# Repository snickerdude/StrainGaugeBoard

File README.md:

# StrainGaugeBoard
Multi channel strain gauge data acquisition board

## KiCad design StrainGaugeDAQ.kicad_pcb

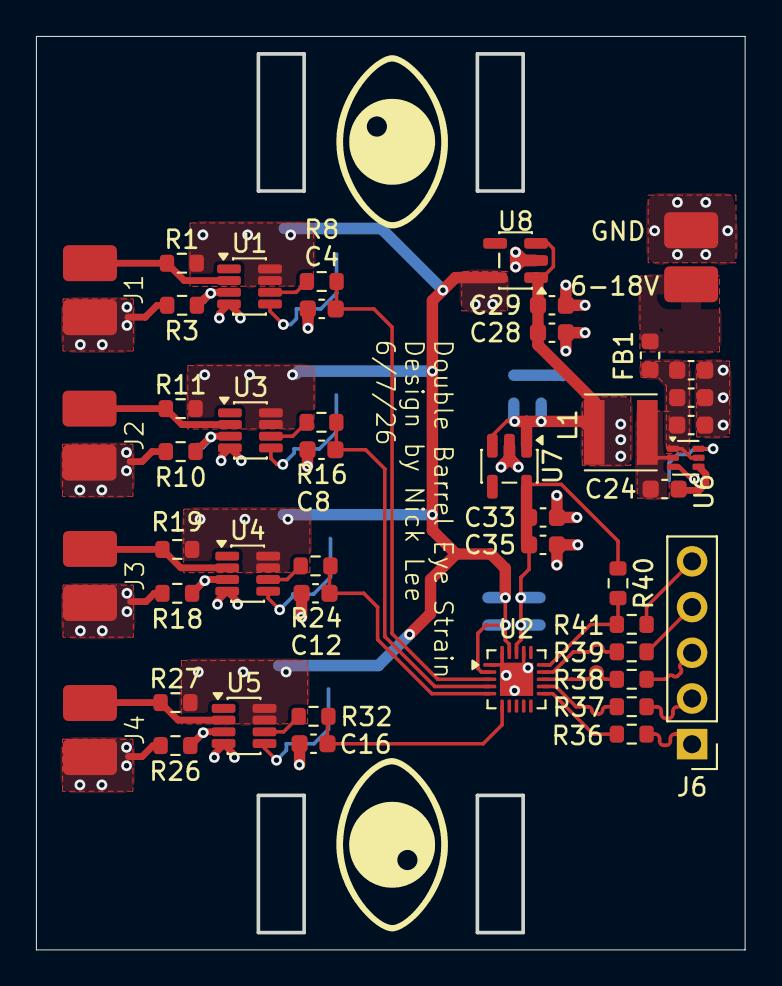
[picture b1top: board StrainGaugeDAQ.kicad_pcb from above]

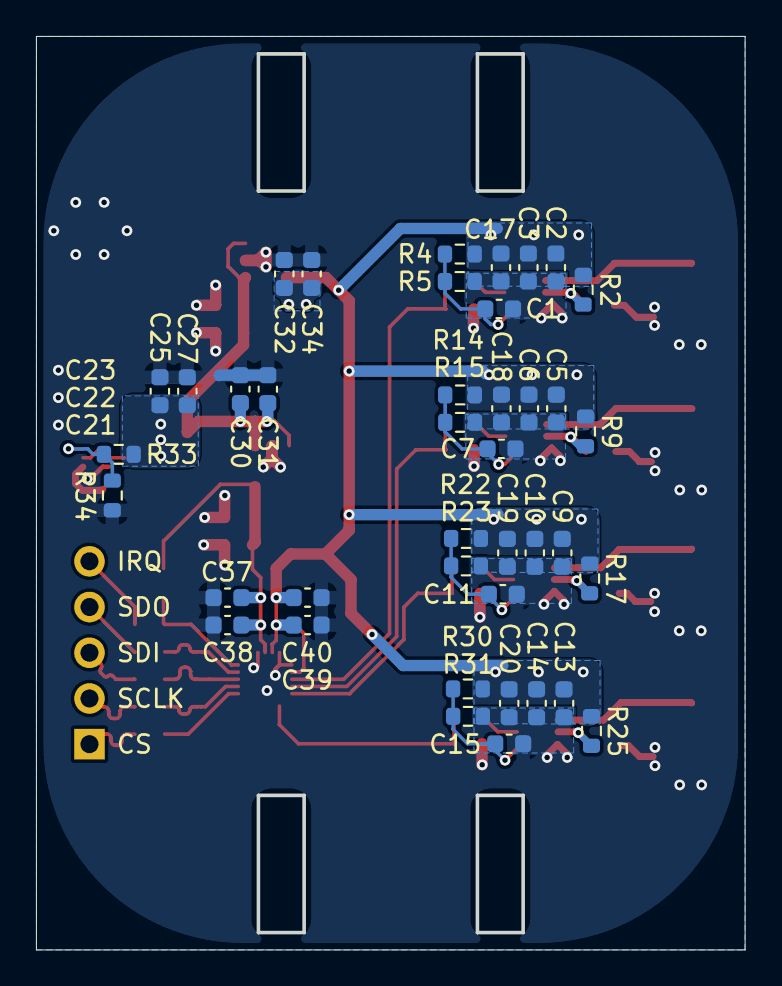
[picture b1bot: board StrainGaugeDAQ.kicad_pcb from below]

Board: 2 copper layers, 39.2 x 50.6 mm, 88 parts (40 on the bottom side), 39 nets.

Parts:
C1, C2, C3, C5, C6, C7, C9, C10, C11, C13, C14, C15, C17, C18, C19, C20, C23, C24, C27, C28, C31, C32, C33, C34, C35, C37, C39: 100n; C_0603_1608Metric
C4, C8, C12, C16: C; C_0603_1608Metric
C21, C22, C25: 22u; C_0603_1608Metric
C29, C30, C38, C40: 10u; C_0603_1608Metric
FB1: FerriteBead; L_0603_1608Metric
H1, H2: MountingScrew; EyePicture
J1: IN1; SolderPad_01x02
J2: IN2; SolderPad_01x02
J3: IN3; SolderPad_01x02
J4: IN4; SolderPad_01x02
J5: 6-18V; SolderPad_01x02
J6: SPI+INT; PinHeader_1x05_P2.54mm_Vertical
L1: 3.3u; L_Vishay_IFSC-1515AH_4x4x1.8mm
R1, R2, R3, R8, R9, R10, R11, R16, R17, R18, R19, R24, R25, R26, R27, R32: R_US; R_0603_1608Metric
R4, R5, R14, R15, R22, R23, R30, R31, R34, R40: 10k; R_0603_1608Metric
R33: 52.3k; R_0603_1608Metric
R36, R37, R38, R39, R41: 10; R_0603_1608Metric
U1, U3, U4, U5: INA351CDSIDSGR; TSOT-23-8
U2: MCP3562RT-E/NC; UQFN-20-1EP_3x3mm_P0.4mm_EP1.85x1.85mm
U6: AP62150Z6; SOT-563
U7, U8: AP2127K-3.3; SOT-23-5

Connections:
5V: C25.1, C27.1, C28.1, C29.1, C30.1, C31.1, L1.2, R33.1, U7.1 (VIN), U7.3 (EN), U8.1 (VIN), U8.3 (EN)
/Amp1/In+: J1.2, R1.2, U1.2 (IN-)
/Amp1/Vout: C4.1, R8.1, U2.3 (CH0)
/Amp2/In+: J2.2, R11.2, U3.2 (IN-)
/Amp2/Vout: C8.1, R16.1, U2.4 (CH1)
/Amp3/In+: J3.2, R19.2, U4.2 (IN-)
/Amp3/Vout: C12.1, R24.1, U2.5 (CH2)
/Amp4/In+: J4.2, R27.2, U5.2 (IN-)
/Amp4/Vout: C16.1, R32.1, U2.6 (CH3)
/PD/VCC: FB1.1, J5.2
AVDD: C2.1, C3.1, C5.1, C6.1, C9.1, C10.1, C13.1, C14.1, C17.2, C18.2, C19.2, C20.2, C32.1, C34.1, C39.2, C40.2, R1.1, R2.1, R4.1, R9.1, R11.1, R14.1, R17.1, R19.1, R22.1, R25.1, R27.1, R30.1, U1.7 (V+), U1.8 (*SHDN), U2.2 (REFIN+/OUT), U2.19 (AVDD), U3.7 (V+), U3.8 (*SHDN), U4.7 (V+), U4.8 (*SHDN), U5.7 (V+), U5.8 (*SHDN), U8.5 (VOUT)
DVDD: C33.1, C35.1, C37.2, C38.2, R40.1, U2.18 (DVDD), U7.5 (VOUT)
GND: C1.2, C2.2, C3.2, C4.2, C5.2, C6.2, C7.2, C8.2, C9.2, C10.2, C11.2, C12.2, C13.2, C14.2, C15.2, C16.2, C17.1, C18.1, C19.1, C20.1, C21.2, C22.2, C23.2, C25.2, C27.2, C28.2, C29.2, C30.2, C31.2, C32.2, C33.2, C34.2, C35.2, C37.1, C38.1, C39.1, C40.1, J1.1, J2.1, J3.1, J4.1, J5.1, R3.2, R5.2, R10.2, R15.2, R18.2, R23.2, R26.2, R31.2, R34.2, U1.4 (V-), U2.1 (REFIN-), U2.17 (DGND), U2.20 (AGND), U2.21 (GND), U3.4 (V-), U4.4 (V-), U5.4 (V-), U6.3 (GND), U7.2 (GND), U8.2 (GND)
unnamed: J6.1, R36.2
unnamed: J6.2, R37.2
unnamed: J6.3, R38.2
unnamed: J6.4, R39.1
unnamed: J6.5, R41.1
unnamed: R2.2, R3.1, U1.3 (IN+)
unnamed: R8.2, U1.6 (OUT)
unnamed: C1.1, R4.2, R5.1, U1.5 (REF)
unnamed: R36.1, U2.11 (*CS)
unnamed: R40.2, R41.2, U2.15 (*IRQ/MDAT)
unnamed: R37.1, U2.12 (SCK)
unnamed: R38.1, U2.13 (SDI)
unnamed: R39.2, U2.14 (SDO)
unnamed: R9.2, R10.1, U3.3 (IN+)
unnamed: R16.2, U3.6 (OUT)
unnamed: C7.1, R14.2, R15.1, U3.5 (REF)
unnamed: R17.2, R18.1, U4.3 (IN+)
unnamed: R24.2, U4.6 (OUT)
unnamed: C11.1, R22.2, R23.1, U4.5 (REF)
unnamed: R25.2, R26.1, U5.3 (IN+)
unnamed: R32.2, U5.6 (OUT)
unnamed: C15.1, R30.2, R31.1, U5.5 (REF)
unnamed: C24.2, U6.4 (BST)
unnamed: C21.1, C22.1, C23.1, FB1.2, U6.1 (VIN), U6.5 (EN)
unnamed: R33.2, R34.1, U6.6 (FB)
unnamed: C24.1, L1.1, U6.2 (SW)

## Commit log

2026-06-02 Scem work
2026-06-06 Schematic done
2026-06-07 Layout work
2026-06-08 fab files created
2026-06-10 BOM generated
